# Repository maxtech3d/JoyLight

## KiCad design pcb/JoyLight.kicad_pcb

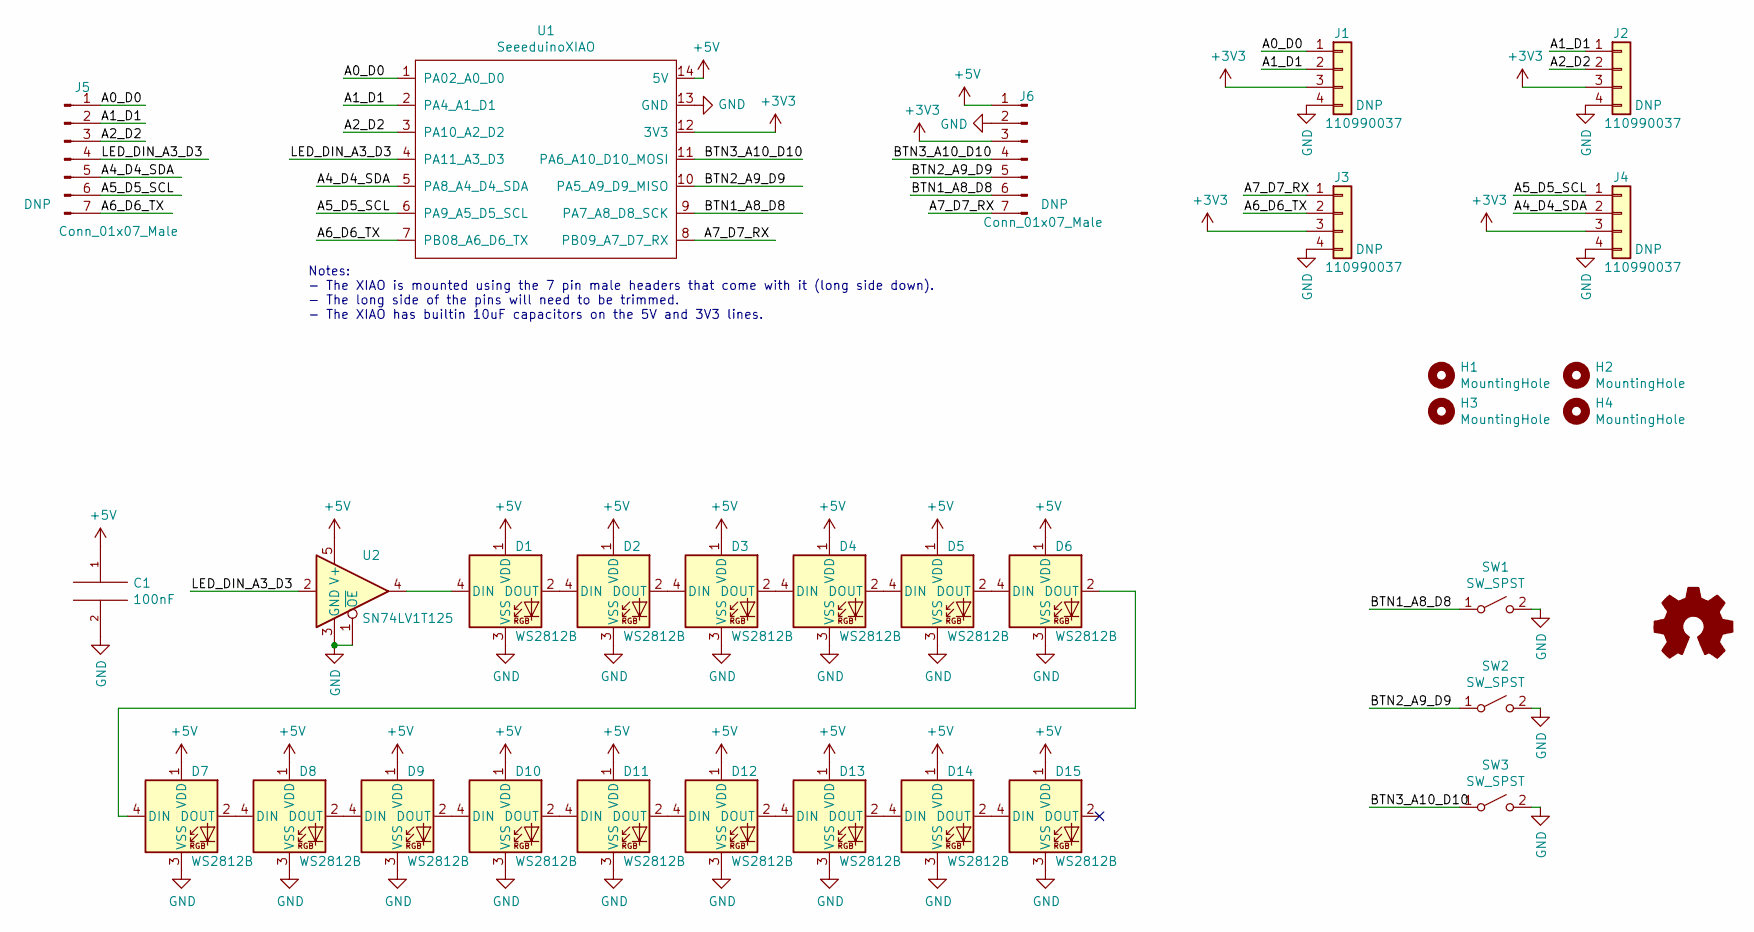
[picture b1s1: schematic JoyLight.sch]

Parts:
C1: 100nF; C_0805_2012Metric; MPN CC0805KRX7R9BB104; LCSC C49678
D1, D2, D3, D4, D5, D6, D7, D8, D9, D10, D11, D12, D13, D14, D15: WS2812B; LED_WS2812B_PLCC4_5.0x5.0mm_P3.2mm; MPN WS2812B-B; LCSC C114586
H1, H2, H3, H4: MountingHole; MountingHole_3.2mm_M3
J1, J2, J3, J4: 110990037; Grove_110990037; MPN 110990037
J5, J6: Conn_01x07_Male; PinHeader_1x07_P2.54mm_Vertical
SW1, SW2, SW3: SW_SPST; Tactile_Switch_TS-1187A-C-G-B; MPN TS-1187A-C-G-B; LCSC C318886
U1: SeeeduinoXIAO; Seeeduino_XIAO
U2: SN74LV1T125; SOT-23-5; MPN SN74LV1T125DBVR; LCSC C473338

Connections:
+3V3: J1.3, J2.3, J3.3, J4.3, J6.3, U1.12 (3V3)
+5V: C1.1, D1.1 (VDD), D2.1 (VDD), D3.1 (VDD), D4.1 (VDD), D5.1 (VDD), D6.1 (VDD), D7.1 (VDD), D8.1 (VDD), D9.1 (VDD), D10.1 (VDD), D11.1 (VDD), D12.1 (VDD), D13.1 (VDD), D14.1 (VDD), D15.1 (VDD), J6.1, U1.14 (5V), U2.5 (V+)
/A0_D0: J1.1, J5.1, U1.1 (PA02_A0_D0)
/A1_D1: J1.2, J2.1, J5.2, U1.2 (PA4_A1_D1)
/A2_D2: J2.2, J5.3, U1.3 (PA10_A2_D2)
/A4_D4_SDA: J4.2, J5.5, U1.5 (PA8_A4_D4_SDA)
/A5_D5_SCL: J4.1, J5.6, U1.6 (PA9_A5_D5_SCL)
/A6_D6_TX: J3.2, J5.7, U1.7 (PB08_A6_D6_TX)
/A7_D7_RX: J3.1, J6.7, U1.8 (PB09_A7_D7_RX)
/BTN1_A8_D8: J6.6, SW1.1 (A), U1.9 (PA7_A8_D8_SCK)
/BTN2_A9_D9: J6.5, SW2.1 (A), U1.10 (PA5_A9_D9_MISO)
/BTN3_A10_D10: J6.4, SW3.1 (A), U1.11 (PA6_A10_D10_MOSI)
/LED_DIN_A3_D3: J5.4, U1.4 (PA11_A3_D3), U2.2
GND: C1.2, D1.3 (VSS), D2.3 (VSS), D3.3 (VSS), D4.3 (VSS), D5.3 (VSS), D6.3 (VSS), D7.3 (VSS), D8.3 (VSS), D9.3 (VSS), D10.3 (VSS), D11.3 (VSS), D12.3 (VSS), D13.3 (VSS), D14.3 (VSS), D15.3 (VSS), J1.4, J2.4, J3.4, J4.4, J6.2, SW1.2 (B), SW2.2 (B), SW3.2 (B), U1.13 (GND), U2.1 (~OE), U2.3 (GND)
unnamed: D1.2 (DOUT), D2.4 (DIN)
unnamed: D1.4 (DIN), U2.4
unnamed: D2.2 (DOUT), D3.4 (DIN)
unnamed: D3.2 (DOUT), D4.4 (DIN)
unnamed: D4.2 (DOUT), D5.4 (DIN)
unnamed: D5.2 (DOUT), D6.4 (DIN)
unnamed: D6.2 (DOUT), D7.4 (DIN)
unnamed: D7.2 (DOUT), D8.4 (DIN)
unnamed: D8.2 (DOUT), D9.4 (DIN)
unnamed: D10.2 (DOUT), D11.4 (DIN)
unnamed: D9.2 (DOUT), D10.4 (DIN)
unnamed: D11.2 (DOUT), D12.4 (DIN)
unnamed: D12.2 (DOUT), D13.4 (DIN)
unnamed: D13.2 (DOUT), D14.4 (DIN)
unnamed: D14.2 (DOUT), D15.4 (DIN)

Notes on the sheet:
Notes: - The XIAO is mounted using the 7 pin male headers that come with it (long side down). - The long side of the pins will need to be trimmed. - The XIAO has builtin 10uF capacitors on the 5V and 3V3 lines.

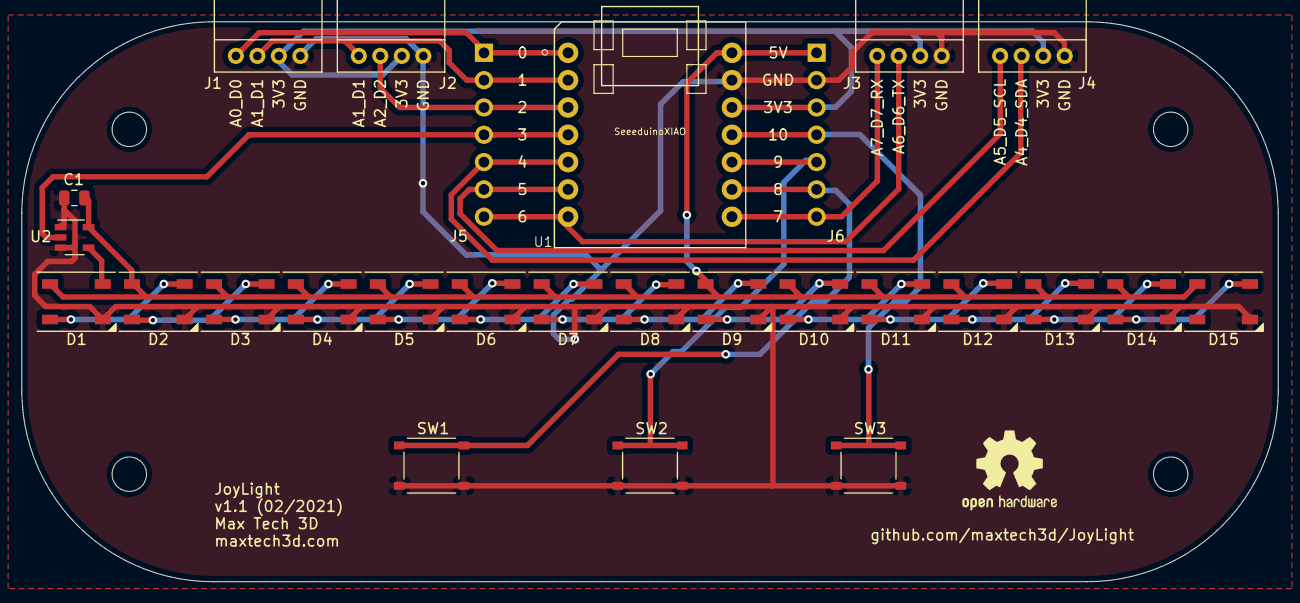
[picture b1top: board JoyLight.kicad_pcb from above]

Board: 2 copper layers, 116.8 x 52.1 mm, 31 parts (0 on the bottom side), 29 nets.

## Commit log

2021-01-17 Created the PCB project
2021-01-17 Work in progress on the schematic
2021-01-18 Finalizing the Schematic and PCB layout for the JoyLight
2021-01-18 Getting the PCB ready for production
    Updated the part numbers
    Added silkscreen info
2021-01-21 Finished V1.0 of the PCB
2021-02-23 Changed the mounting method of the Xiao
    The Xiao is now mounted by using the pin headers supplied with it instead of directly soldering it to the board
2021-02-24 PCB finishing touches
    - added mounting points
    - added the OSHW logo
2021-02-24 Updated schematic
    Missed these files in the previous commit
2021-02-24 Joylight v1.1 PCB
    - minor changes for preparing the board for production
2021-02-28 Initial firmware commit
2021-02-28 Recovered the schematic
    KiCad messed it up for some reason, had to recover from the backup file
2021-02-28 Added the step model of the PCB
2021-03-16 Added LED animations to the firmware
2021-03-16 Fixed display on animation bug
    The display wouldn't turn off if there was an animation in progress
2021-03-18 Updated the default colors
2021-03-22 Updated the colors and animations
2021-04-06 Adjusted the color order
2021-04-06 Added ability to force max brightness on long button press
2021-04-18 Added electronics assembly instructions
2021-04-18 Uploaded the 3D models
2021-04-18 Added 3D printing instructions. Renamed the 3d printing files
2021-04-18 Fixed broken link
2021-04-18 Enclosure assembly instructions
2021-04-18 Added programming instructions
